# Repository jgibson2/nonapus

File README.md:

# nonapus
Control board for 9 servos. Based on Teensy 3.2.

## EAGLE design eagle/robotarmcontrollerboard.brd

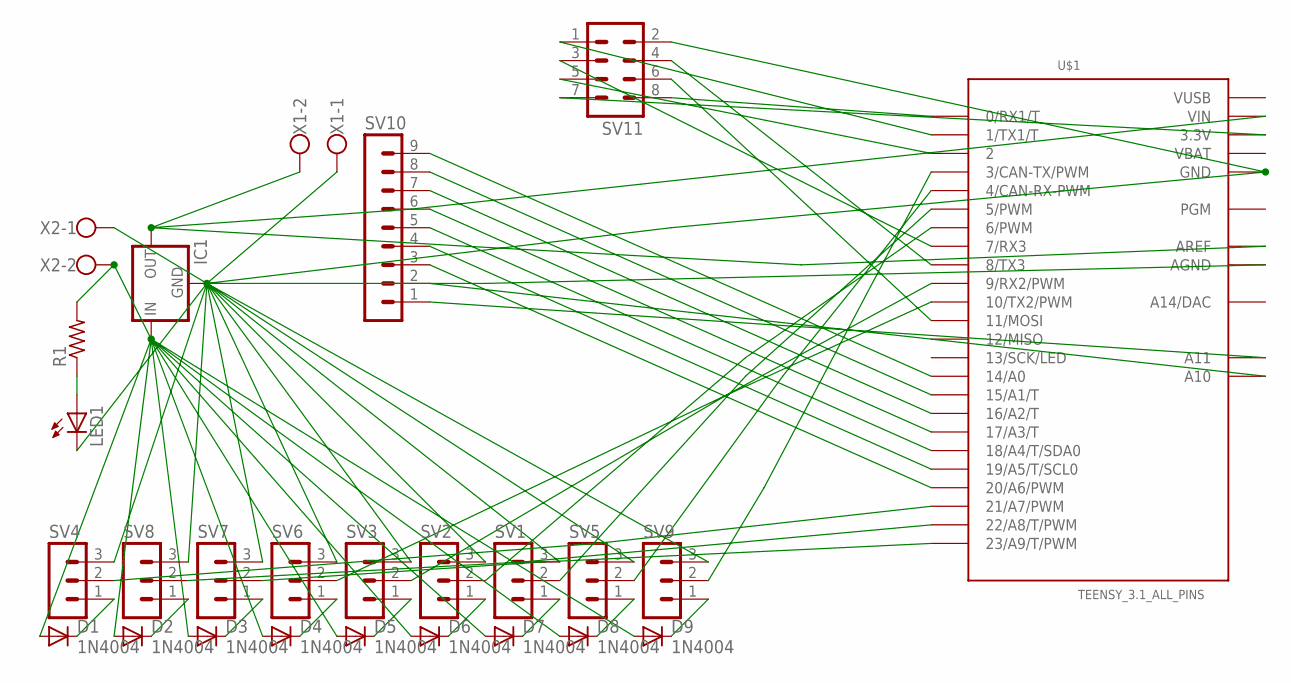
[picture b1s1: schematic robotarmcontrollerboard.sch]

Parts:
D1, D2, D3, D4, D5, D6, D7, D8, D9: 1N4004; DO41-10
IC1: 78XXL
LED1: LED3MM
R1: R-US_0204/7; 0204/7
SV1, SV2, SV3, SV4, SV5, SV6, SV7, SV8, SV9: MA03-1
SV10: MA09-1W
SV11: MA04-2
U$1: TEENSY_3.1_ALL_PINS; TEENSY3-ALL_PINS
X1, X2: W237-102

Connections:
unnamed: SV10.9, U$1.14/A0
unnamed: SV10.8, U$1.15/A1 (15/A1/T)
unnamed: SV10.7, U$1.16/A2 (16/A2/T)
unnamed: SV10.6, U$1.17/A3 (17/A3/T)
unnamed: SV10.5, U$1.18/A4 (18/A4/T/SDA0)
unnamed: SV10.4, U$1.19/A5 (19/A5/T/SCL0)
unnamed: SV10.3, U$1.20/A6 (20/A6/PWM)
unnamed: SV10.2, U$1.A10
unnamed: SV10.1, U$1.A11
unnamed: SV9.2, U$1.3 (3/CAN-TX/PWM)
unnamed: SV5.2, U$1.4 (4/CAN-RX-PWM)
unnamed: SV1.2, U$1.5 (5/PWM)
unnamed: SV2.2, U$1.6 (6/PWM)
unnamed: SV3.2, U$1.9 (9/RX2/PWM)
unnamed: SV6.2, U$1.10 (10/TX2/PWM)
unnamed: SV7.2, U$1.23/A9 (23/A9/T/PWM)
unnamed: SV8.2, U$1.22/A8 (22/A8/T/PWM)
unnamed: SV4.2, U$1.21/A7 (21/A7/PWM)
unnamed: IC1.GND, LED1.K (C), SV1.3, SV2.3, SV3.3, SV4.3, SV5.3, SV6.3, SV7.3, SV8.3, SV9.3, SV11.2, U$1.AGND, U$1.GND, U$1.GND1 (GND), X1.1, X2.1
unnamed: IC1.OUT, U$1.AREF, U$1.VIN, X1.2
unnamed: D1.C, SV4.1
unnamed: D2.C, SV8.1
unnamed: D3.C, SV7.1
unnamed: D4.C, SV6.1
unnamed: D5.C, SV3.1
unnamed: D6.C, SV2.1
unnamed: D7.C, SV1.1
unnamed: D8.C, SV5.1
unnamed: D9.C, SV9.1
unnamed: LED1.A, R1.1
unnamed: SV11.1, U$1.1 (1/TX1/T)
unnamed: D1.A, D2.A, D3.A, D4.A, D5.A, D6.A, D7.A, D8.A, D9.A, IC1.IN, R1.2, X2.2
unnamed: SV11.7, U$1.3.3V, U$1.3.3V1 (3.3V)
unnamed: SV11.5, U$1.2
unnamed: SV11.4, U$1.8 (8/TX3)
unnamed: SV11.6, U$1.11 (11/MOSI)
unnamed: SV11.3, U$1.7 (7/RX3)
unnamed: SV11.8, U$1.0 (0/RX1/T)
VBAT: U$1.VBAT
VUSB: U$1.VUSB

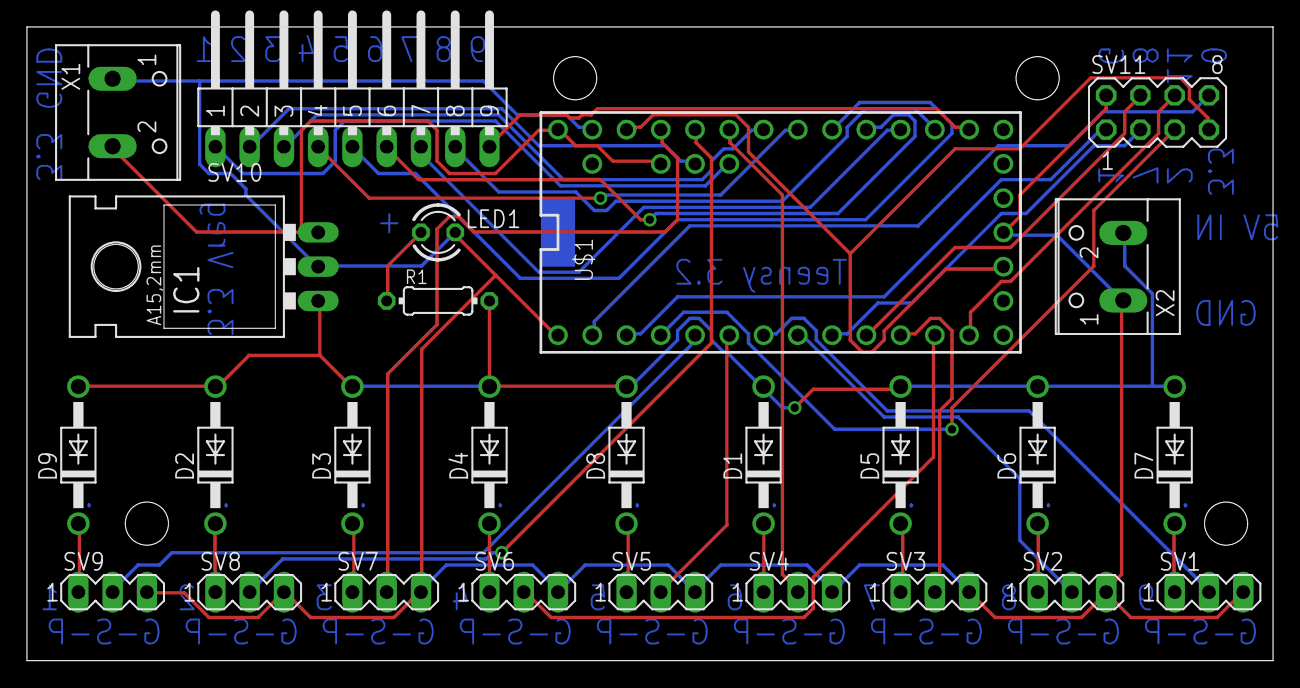
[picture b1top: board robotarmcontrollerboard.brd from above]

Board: 2 copper layers, 92.4 x 47.0 mm, 26 parts (0 on the bottom side), 38 nets.

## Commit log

2016-02-25 Initial framework for repository
